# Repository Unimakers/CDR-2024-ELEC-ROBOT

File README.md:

# CDR-2024-ELEC-ROBOT

L'elec du robot de l'équipe Unimakers

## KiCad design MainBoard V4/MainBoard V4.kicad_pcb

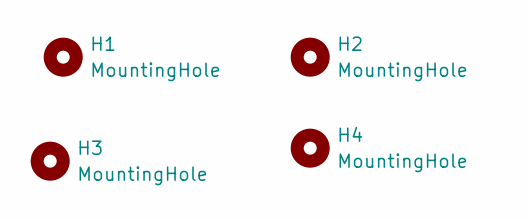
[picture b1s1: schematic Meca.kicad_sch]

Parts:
H1, H2, H3, H4: MountingHole; MountingHole_3.2mm_M3

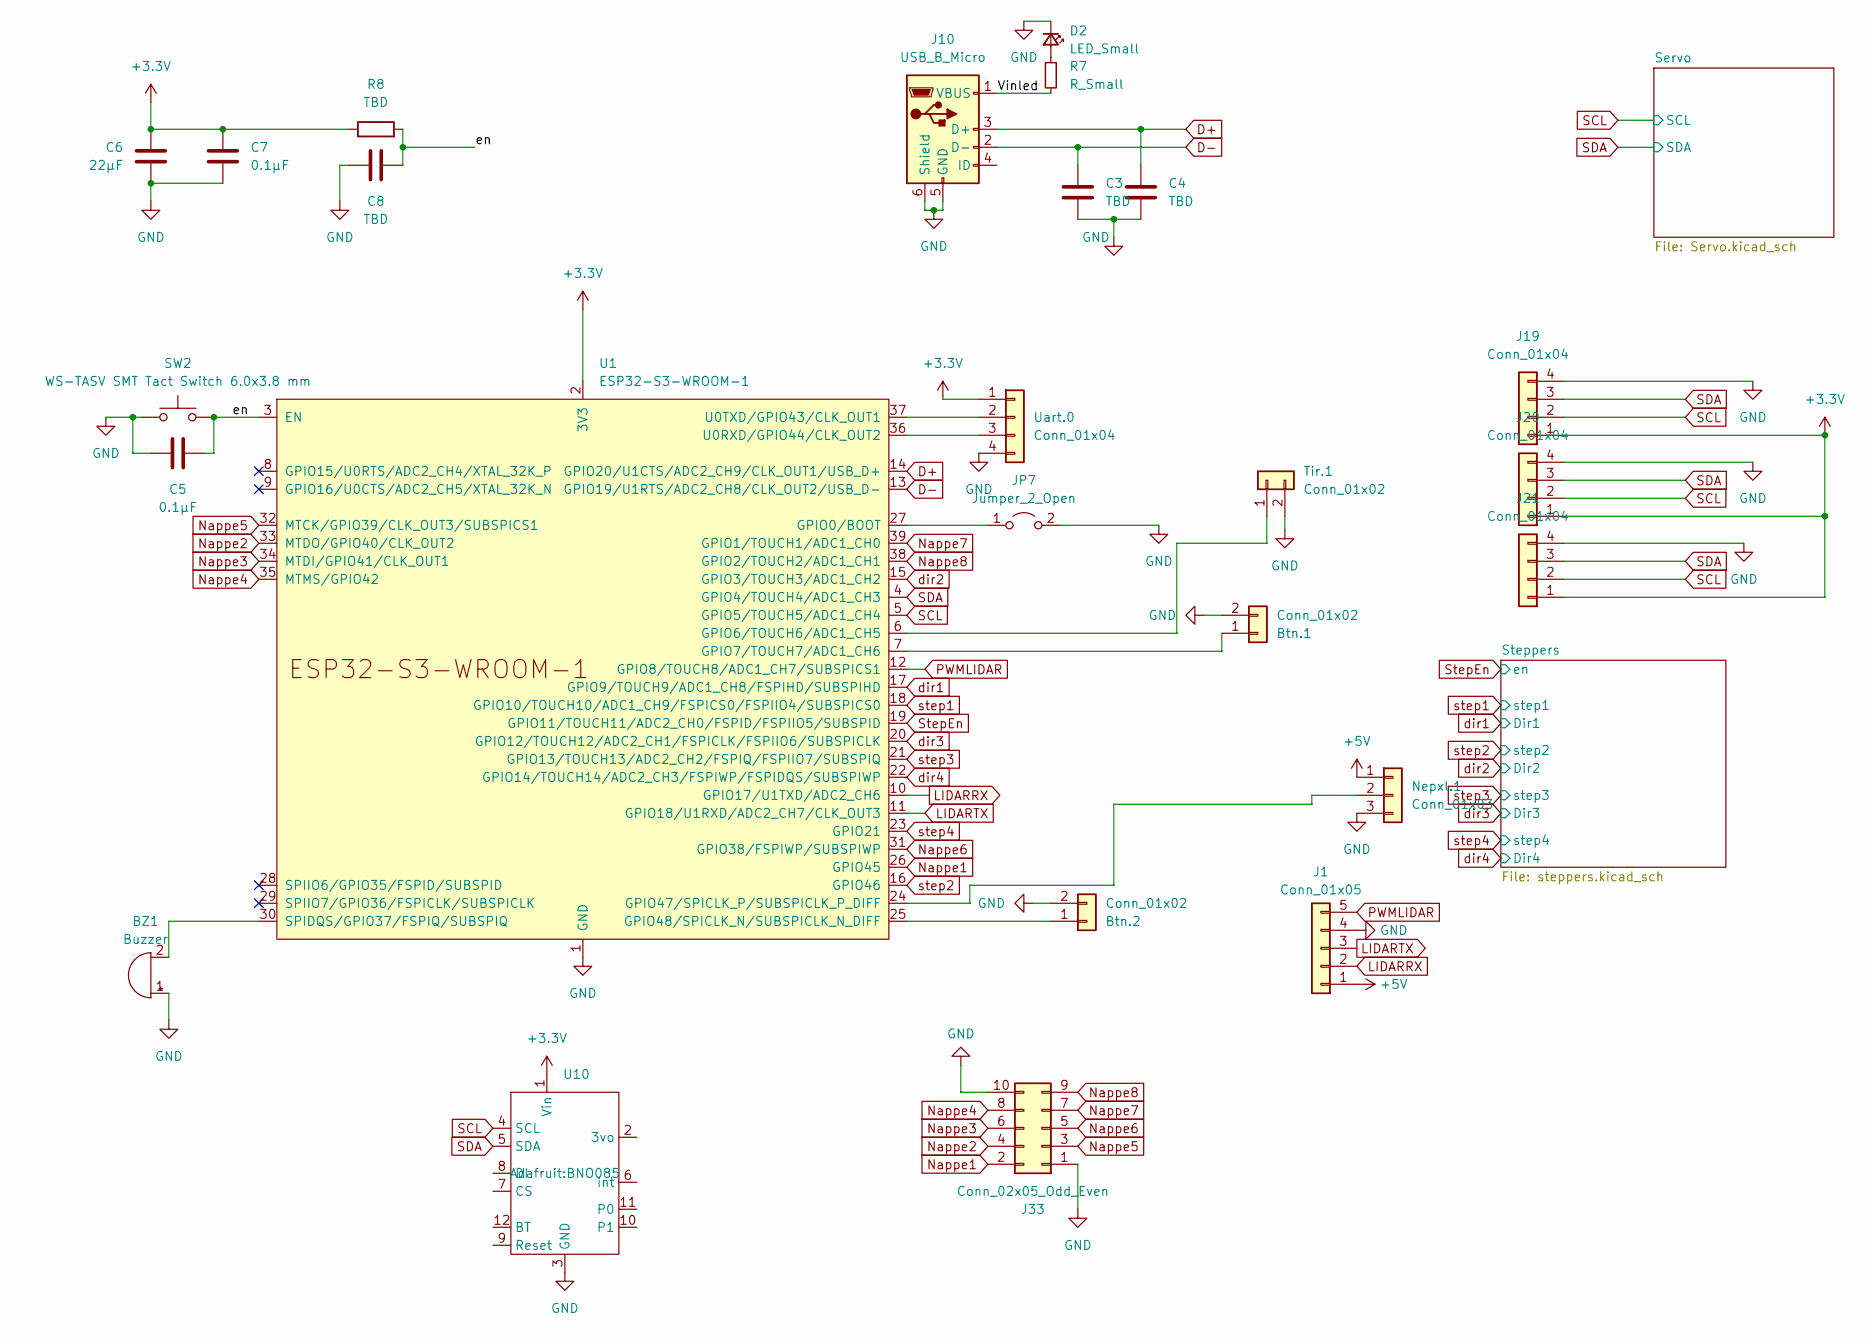
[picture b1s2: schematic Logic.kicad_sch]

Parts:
BZ1: Buzzer; Buzzer_12x9.5RM7.6
Btn.1, Btn.2: Conn_01x02; JST_XH_B2B-XH-A_1x02_P2.50mm_Vertical
C3, C4, C8: TBD; C_0805_2012Metric_Pad1.18x1.45mm_HandSolder
C5, C7: 0.1µF; C_0805_2012Metric_Pad1.18x1.45mm_HandSolder
C6: 22µF; C_0805_2012Metric_Pad1.18x1.45mm_HandSolder
D2: LED_Small; LED_1206_3216Metric_Pad1.42x1.75mm_HandSolder
J1: Conn_01x05; JST_XH_B5B-XH-A_1x05_P2.50mm_Vertical
J10: USB_B_Micro; USB_Micro-B_Wuerth_629105150521
J19, J20, J21: Conn_01x04; JST_XH_B4B-XH-A_1x04_P2.50mm_Vertical
J33: Conn_02x05_Odd_Even; IDC-Header_2x05_P2.54mm_Vertical
JP7: Jumper_2_Open; PinHeader_1x02_P2.54mm_Vertical
Nepxl.1: Conn_01x03; PinSocket_1x03_P2.54mm_Vertical
R7: R_Small; R_1206_3216Metric_Pad1.30x1.75mm_HandSolder
R8: TBD; R_1206_3216Metric_Pad1.30x1.75mm_HandSolder
SW2: WS-TASV SMT Tact Switch 6.0x3.8 mm; WS-TASV SMT Tact Switch
Tir.1: Conn_01x02; JST_XH_B2B-XH-A_1x02_P2.50mm_Vertical
U1: ESP32-S3-WROOM-1
U10: BNO085
Uart.0: Conn_01x04; JST_XH_B4B-XH-A_1x04_P2.50mm_Vertical

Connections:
+3.3V: C6.2, C7.2, J19.1, J20.1, J21.1, R8.1, U1.2 (3V3), U10.1 (Vin), Uart.0.1; also elsewhere on the board
+5V: J1.1, Nepxl.1.1; also elsewhere on the board
/Logic/Vinled: J10.1 (VBUS), R7.2
/Logic/en: C5.2, C8.1, R8.2, SW2.2, U1.3 (EN)
D+: C4.1, J10.3 (D+), U1.14 (GPIO20/U1CTS/ADC2_CH9/CLK_OUT1/USB_D+)
D-: C3.1, J10.2 (D-), U1.13 (GPIO19/U1RTS/ADC2_CH8/CLK_OUT2/USB_D-)
GND: BZ1.1 (-), Btn.1.2, Btn.2.2, C3.2, C4.2, C5.1, C6.1, C7.1, C8.2, D2.1 (K), J1.4, J10.5 (GND), J10.6 (Shield), J19.4, J20.4, J21.4, J33.1, J33.10, JP7.2 (B), Nepxl.1.3, SW2.1, Tir.1.2, U1.1 (GND), U1.40 (GND), U1.41 (GND), U10.3 (GND), Uart.0.4; also elsewhere on the board
LIDARRX: J1.2, U1.10 (GPIO17/U1TXD/ADC2_CH6)
LIDARTX: J1.3, U1.11 (GPIO18/U1RXD/ADC2_CH7/CLK_OUT3)
Nappe1: J33.2, U1.26 (GPIO45)
Nappe2: J33.4, U1.33 (MTDO/GPIO40/CLK_OUT2)
Nappe3: J33.6, U1.34 (MTDI/GPIO41/CLK_OUT1)
Nappe4: J33.8, U1.35 (MTMS/GPIO42)
Nappe5: J33.3, U1.32 (MTCK/GPIO39/CLK_OUT3/SUBSPICS1)
Nappe6: J33.5, U1.31 (GPIO38/FSPIWP/SUBSPIWP)
Nappe7: J33.7, U1.39 (GPIO1/TOUCH1/ADC1_CH0)
Nappe8: J33.9, U1.38 (GPIO2/TOUCH2/ADC1_CH1)
unnamed: BZ1.2 (+), U1.30 (SPIDQS/GPIO37/FSPIQ/SUBSPIQ)
unnamed: Btn.1.1, U1.7 (GPIO7/TOUCH7/ADC1_CH6)
unnamed: Btn.2.1, U1.25 (GPIO48/SPICLK_N/SUBSPICLK_N_DIFF)
unnamed: D2.2 (A), R7.1
unnamed: JP7.1 (A), U1.27 (GPIO0/BOOT)
unnamed: Nepxl.1.2, U1.24 (GPIO47/SPICLK_P/SUBSPICLK_P_DIFF)
unnamed: Tir.1.1, U1.6 (GPIO6/TOUCH6/ADC1_CH5)
unnamed: U1.36 (U0RXD/GPIO44/CLK_OUT2), Uart.0.3
unnamed: U1.37 (U0TXD/GPIO43/CLK_OUT1), Uart.0.2
PWMLIDAR: J1.5, U1.12 (GPIO8/TOUCH8/ADC1_CH7/SUBSPICS1)
SCL: J19.2, J20.2, J21.2, U1.5 (GPIO5/TOUCH5/ADC1_CH4), U10.4 (SCL); also elsewhere on the board
SDA: J19.3, J20.3, J21.3, U1.4 (GPIO4/TOUCH4/ADC1_CH3), U10.5 (SDA); also elsewhere on the board
StepEn: U1.19 (GPIO11/TOUCH11/ADC2_CH0/FSPID/FSPIIO5/S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); also elsewhere on the board
dir1: U1.17 (GPIO9/TOUCH9/ADC1_CH8/FSPIHD/SUBSPIHD); also elsewhere on the board
dir2: U1.15 (GPIO3/TOUCH3/ADC1_CH2); also elsewhere on the board
dir3: U1.20 (GPIO12/TOUCH12/ADC2_CH1/FSPICLK/FSPIIO6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); also elsewhere on the board
dir4: U1.22 (GPIO14/TOUCH14/ADC2_CH3/FSPIWP/FSPIDQS/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); also elsewhere on the board
step1: U1.18 (GPIO10/TOUCH10/ADC1_CH9/FSPICS0/FSPIIO4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); also elsewhere on the board
step2: U1.16 (GPIO46); also elsewhere on the board
step3: U1.21 (GPIO13/TOUCH13/ADC2_CH2/FSPIQ/FSPIIO7/S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); also elsewhere on the board
step4: U1.23 (GPIO21); also elsewhere on the board

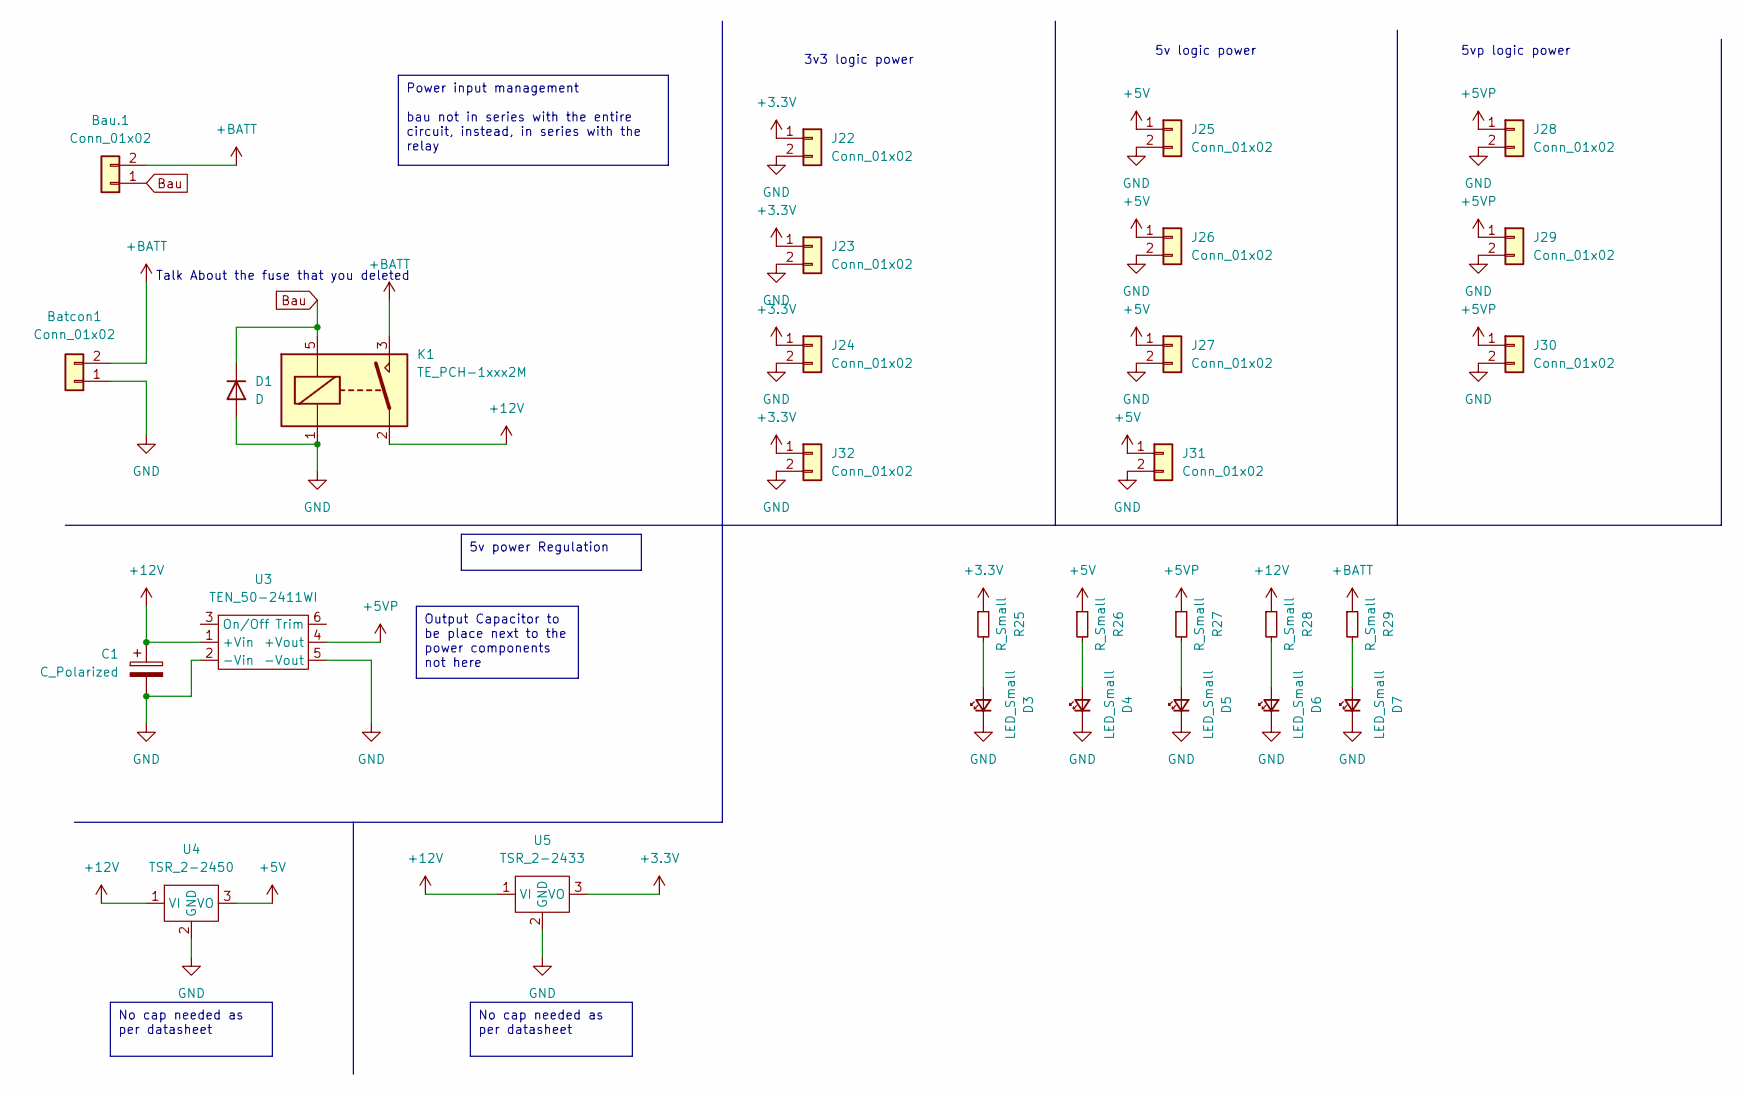
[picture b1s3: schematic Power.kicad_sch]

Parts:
Batcon1: Conn_01x02; AMASS_XT60-F_1x02_P7.20mm_Vertical
Bau.1: Conn_01x02; Molex_KK-254_AE-6410-02A_1x02_P2.54mm_Vertical
C1: C_Polarized
D1: D; D_DO-35_SOD27_P10.16mm_Horizontal
D3, D4, D5, D6, D7: LED_Small; LED_1206_3216Metric_Pad1.42x1.75mm_HandSolder
J22, J23, J24, J25, J26, J27, J28, J29, J30, J31, J32: Conn_01x02; Molex_KK-254_AE-6410-02A_1x02_P2.54mm_Vertical
K1: TE_PCH-1xxx2M; Relay_SPST_TE_PCH-1xxx2M
R25, R26, R27, R28, R29: R_Small; LED_1206_3216Metric_Pad1.42x1.75mm_HandSolder
U3: TEN_50-2411WI; Traco TEN 50 series
U4: TSR_2-2450; Traco 2- 24xx
U5: TSR_2-2433; Traco 2- 24xx

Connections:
+3.3V: J22.1, J23.1, J24.1, J32.1, R25.1, U5.3 (VO); also elsewhere on the board
+5V: J25.1, J26.1, J27.1, J31.1, R26.1, U4.3 (VO); also elsewhere on the board
+5VP: J28.1, J29.1, J30.1, R27.1, U3.4 (+Vout); also elsewhere on the board
+12V: C1.1, K1.2, R28.1, U3.1 (+Vin), U4.1 (VI), U5.1 (VI); also elsewhere on the board
+BATT: Batcon1.2, Bau.1.2, K1.3, R29.1
Bau: Bau.1.1, D1.1 (K), K1.5
GND: Batcon1.1, C1.2, D1.2 (A), D3.1 (K), D4.1 (K), D5.1 (K), D6.1 (K), D7.1 (K), J22.2, J23.2, J24.2, J25.2, J26.2, J27.2, J28.2, J29.2, J30.2, J31.2, J32.2, K1.1, U3.2 (-Vin), U3.5 (-Vout), U4.2 (GND), U5.2 (GND); also elsewhere on the board
unnamed: D3.2 (A), R25.2
unnamed: D4.2 (A), R26.2
unnamed: D5.2 (A), R27.2
unnamed: D6.2 (A), R28.2
unnamed: D7.2 (A), R29.2

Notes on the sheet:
Output Capacitor to be place next to the power components not here
5v power Regulation
No cap needed as per datasheet
Power input management bau not in series with the entire circuit, instead, in series with the relay
5vp logic power
Talk About the fuse that you deleted
5v logic power
3v3 logic power

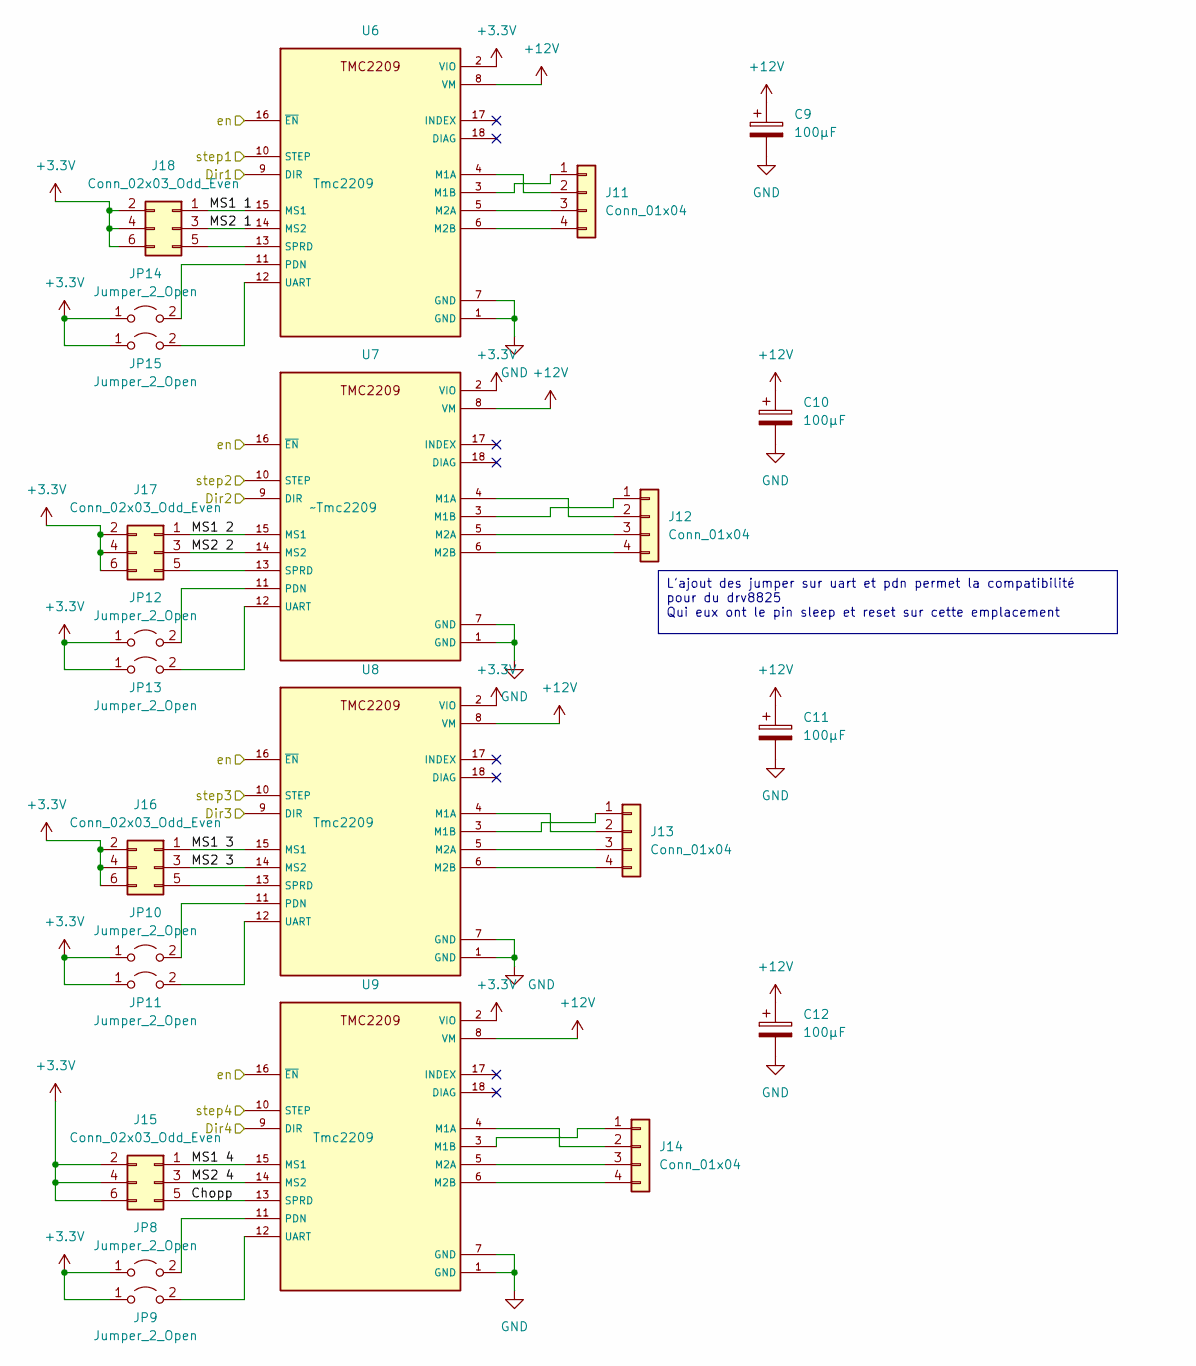
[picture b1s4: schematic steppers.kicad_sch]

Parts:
C9, C10, C11, C12: 100µF; CP_Elec_10x10.5
J11, J12, J13, J14: Conn_01x04; Molex_KK-254_AE-6410-04A_1x04_P2.54mm_Vertical
J15, J16, J17, J18: Conn_02x03_Odd_Even; PinHeader_2x03_P2.54mm_Vertical
JP8, JP9, JP10, JP11, JP12, JP13, JP14, JP15: Jumper_2_Open; SolderJumper-2_P1.3mm_Open_Pad1.0x1.5mm
U6, U8, U9: Tmc2209; BOB_TMC2209_SILENTSTEPSTICK
U7: ~Tmc2209; BOB_TMC2209_SILENTSTEPSTICK

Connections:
+3.3V: J15.2, J15.4, J15.6, J16.2, J16.4, J16.6, J17.2, J17.4, J17.6, J18.2, J18.4, J18.6, JP8.1 (A), JP9.1 (A), JP10.1 (A), JP11.1 (A), JP12.1 (A), JP13.1 (A), JP14.1 (A), JP15.1 (A), U6.2 (VIO), U7.2 (VIO), U8.2 (VIO), U9.2 (VIO); also elsewhere on the board
+12V: C9.1, C10.1, C11.1, C12.1, U6.8 (VM), U7.8 (VM), U8.8 (VM), U9.8 (VM); also elsewhere on the board
/Logic/Steppers/Chopp: J15.5, U9.13 (SPRD)
/Logic/Steppers/MS1 1: J18.1, U6.15 (MS1)
/Logic/Steppers/MS1 2: J17.1, U7.15 (MS1)
/Logic/Steppers/MS1 3: J16.1, U8.15 (MS1)
/Logic/Steppers/MS1 4: J15.1, U9.15 (MS1)
/Logic/Steppers/MS2 1: J18.3, U6.14 (MS2)
/Logic/Steppers/MS2 2: J17.3, U7.14 (MS2)
/Logic/Steppers/MS2 3: J16.3, U8.14 (MS2)
/Logic/Steppers/MS2 4: J15.3, U9.14 (MS2)
GND: C9.2, C10.2, C11.2, C12.2, U6.1 (GND), U6.7 (GND), U7.1 (GND), U7.7 (GND), U8.1 (GND), U8.7 (GND), U9.1 (GND), U9.7 (GND); also elsewhere on the board
unnamed: J11.1, U6.3 (M1B)
unnamed: J11.2, U6.4 (M1A)
unnamed: J11.3, U6.5 (M2A)
unnamed: J11.4, U6.6 (M2B)
unnamed: J12.1, U7.3 (M1B)
unnamed: J12.2, U7.4 (M1A)
unnamed: J12.3, U7.5 (M2A)
unnamed: J12.4, U7.6 (M2B)
unnamed: J13.1, U8.3 (M1B)
unnamed: J13.2, U8.4 (M1A)
unnamed: J13.3, U8.5 (M2A)
unnamed: J13.4, U8.6 (M2B)
unnamed: J14.1, U9.3 (M1B)
unnamed: J14.2, U9.4 (M1A)
unnamed: J14.3, U9.5 (M2A)
unnamed: J14.4, U9.6 (M2B)
unnamed: J16.5, U8.13 (SPRD)
unnamed: J17.5, U7.13 (SPRD)
unnamed: J18.5, U6.13 (SPRD)
unnamed: JP8.2 (B), U9.11 (PDN)
unnamed: JP9.2 (B), U9.12 (UART)
unnamed: JP10.2 (B), U8.11 (PDN)
unnamed: JP11.2 (B), U8.12 (UART)
unnamed: JP12.2 (B), U7.11 (PDN)
unnamed: JP13.2 (B), U7.12 (UART)
unnamed: JP14.2 (B), U6.11 (PDN)
unnamed: JP15.2 (B), U6.12 (UART)
StepEn: U6.16 (~EN), U7.16 (~EN), U8.16 (~EN), U9.16 (~EN); also elsewhere on the board
dir1: U6.9 (DIR); also elsewhere on the board
dir2: U7.9 (DIR); also elsewhere on the board
dir3: U8.9 (DIR); also elsewhere on the board
dir4: U9.9 (DIR); also elsewhere on the board
step1: U6.10 (STEP); also elsewhere on the board
step2: U7.10 (STEP); also elsewhere on the board
step3: U8.10 (STEP); also elsewhere on the board
step4: U9.10 (STEP); also elsewhere on the board

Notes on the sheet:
L'ajout des jumper sur uart et pdn permet la compatibilité pour du drv8825 Qui eux ont le pin sleep et reset sur cette emplacement

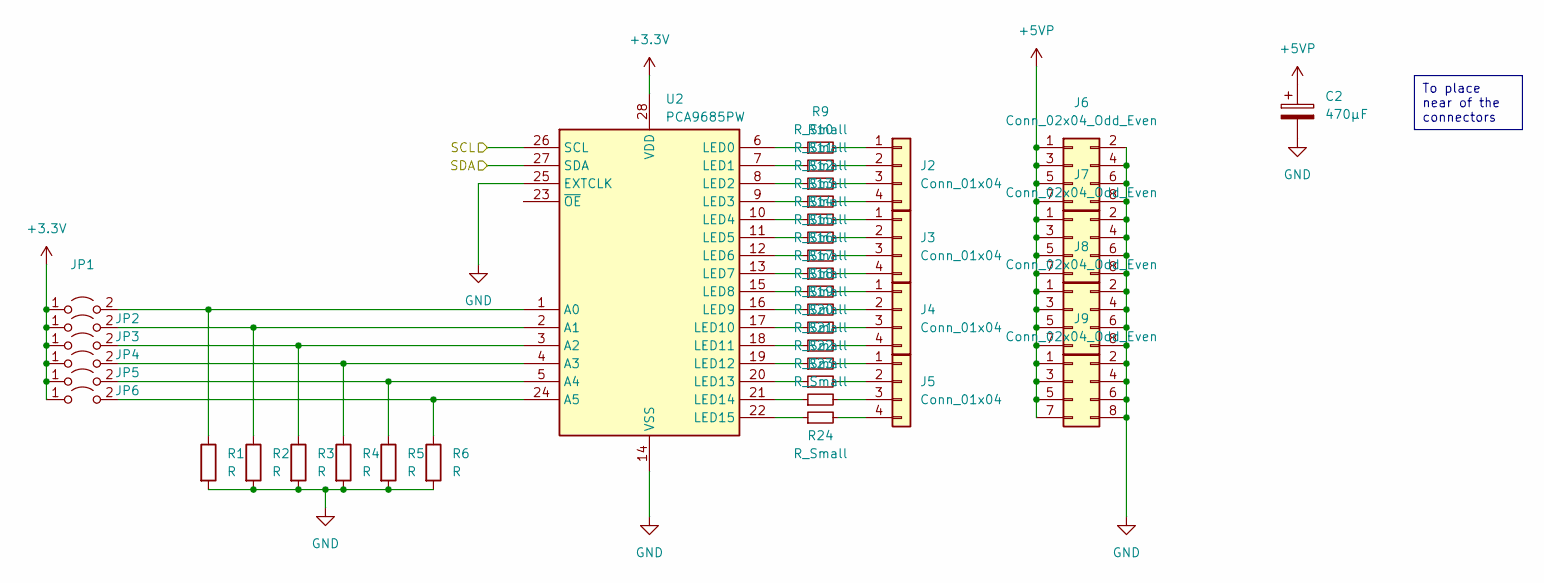
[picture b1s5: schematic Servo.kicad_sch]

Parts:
C2: 470µF; CP_Elec_10x10.5
J2, J3, J4, J5: Conn_01x04; PinHeader_1x04_P2.54mm_Vertical
J6, J7, J8, J9: Conn_02x04_Odd_Even; PinHeader_2x04_P2.54mm_Vertical
JP1, JP2, JP3, JP4, JP5, JP6: Jumper_2_Open; SolderJumper-2_P1.3mm_Open_Pad1.0x1.5mm
R1, R2, R3, R4, R5, R6: R; R_1206_3216Metric_Pad1.30x1.75mm_HandSolder
R9, R10, R11, R12, R13, R14, R15, R16, R17, R18, R19, R20, R21, R22, R23, R24: R_Small; R_1206_3216Metric_Pad1.30x1.75mm_HandSolder
U2: PCA9685PW; TSSOP-28_4.4x9.7mm_P0.65mm

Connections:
+3.3V: JP1.1 (A), JP2.1 (A), JP3.1 (A), JP4.1 (A), JP5.1 (A), JP6.1 (A), U2.28 (VDD); also elsewhere on the board
+5VP: C2.1, J6.1, J6.3, J6.5, J6.7, J7.1, J7.3, J7.5, J7.7, J8.1, J8.3, J8.5, J8.7, J9.1, J9.3, J9.5, J9.7; also elsewhere on the board
GND: C2.2, J6.2, J6.4, J6.6, J6.8, J7.2, J7.4, J7.6, J7.8, J8.2, J8.4, J8.6, J8.8, J9.2, J9.4, J9.6, J9.8, R1.2, R2.2, R3.2, R4.2, R5.2, R6.2, U2.14 (VSS), U2.25 (EXTCLK); also elsewhere on the board
unnamed: J2.1, R9.2
unnamed: J2.2, R10.2
unnamed: J2.3, R11.2
unnamed: J2.4, R12.2
unnamed: J3.1, R13.2
unnamed: J3.2, R14.2
unnamed: J3.3, R15.2
unnamed: J3.4, R16.2
unnamed: J4.1, R17.2
unnamed: J4.2, R18.2
unnamed: J4.3, R19.2
unnamed: J4.4, R20.2
unnamed: J5.1, R21.2
unnamed: J5.2, R22.2
unnamed: J5.3, R23.2
unnamed: J5.4, R24.2
unnamed: JP1.2 (B), R1.1, U2.1 (A0)
unnamed: JP2.2 (B), R2.1, U2.2 (A1)
unnamed: JP3.2 (B), R3.1, U2.3 (A2)
unnamed: JP4.2 (B), R4.1, U2.4 (A3)
unnamed: JP5.2 (B), R5.1, U2.5 (A4)
unnamed: JP6.2 (B), R6.1, U2.24 (A5)
unnamed: R9.1, U2.6 (LED0)
unnamed: R10.1, U2.7 (LED1)
unnamed: R11.1, U2.8 (LED2)
unnamed: R12.1, U2.9 (LED3)
unnamed: R13.1, U2.10 (LED4)
unnamed: R14.1, U2.11 (LED5)
unnamed: R15.1, U2.12 (LED6)
unnamed: R16.1, U2.13 (LED7)
unnamed: R17.1, U2.15 (LED8)
unnamed: R18.1, U2.16 (LED9)
unnamed: R19.1, U2.17 (LED10)
unnamed: R20.1, U2.18 (LED11)
unnamed: R21.1, U2.19 (LED12)
unnamed: R22.1, U2.20 (LED13)
unnamed: R23.1, U2.21 (LED14)
unnamed: R24.1, U2.22 (LED15)
SCL: U2.26 (SCL); also elsewhere on the board
SDA: U2.27 (SDA); also elsewhere on the board

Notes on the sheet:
To place near of the connectors

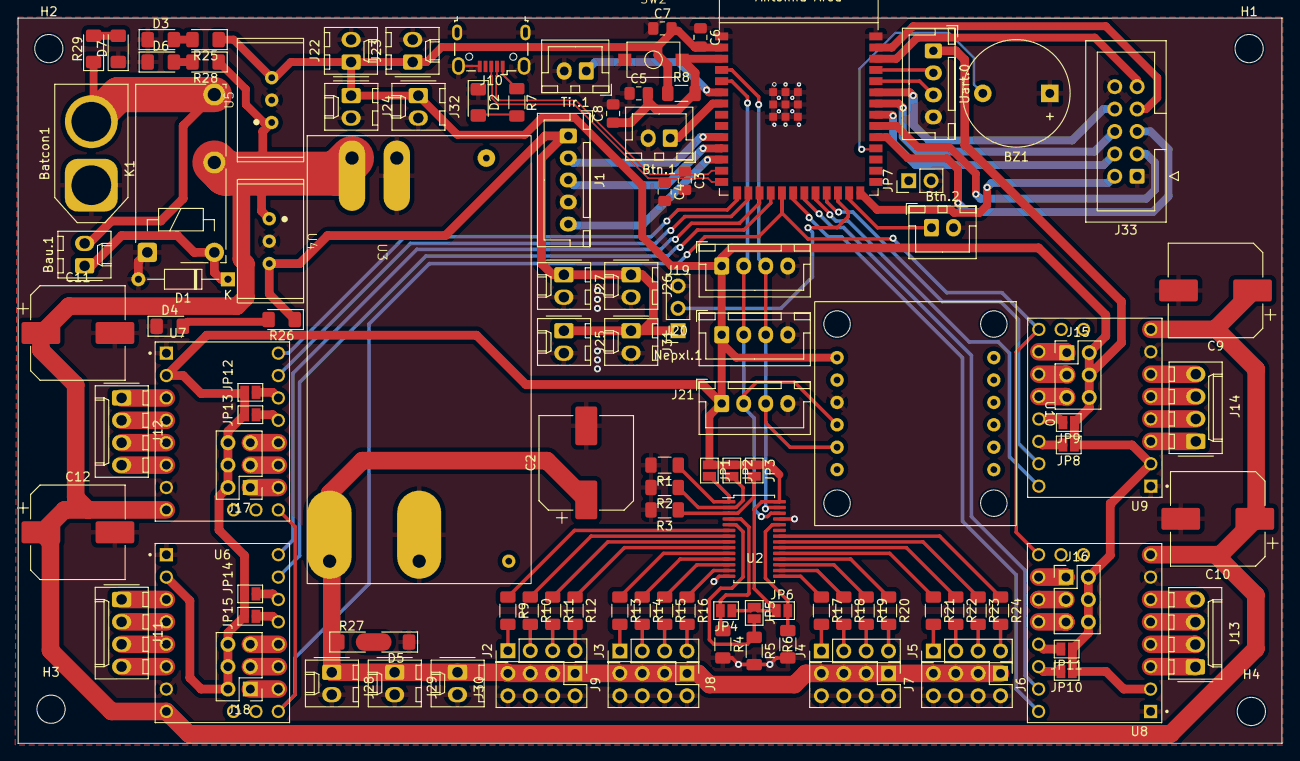
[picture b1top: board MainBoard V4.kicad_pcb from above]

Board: 2 copper layers, 143.3 x 82.3 mm, 119 parts (0 on the bottom side), 121 nets.

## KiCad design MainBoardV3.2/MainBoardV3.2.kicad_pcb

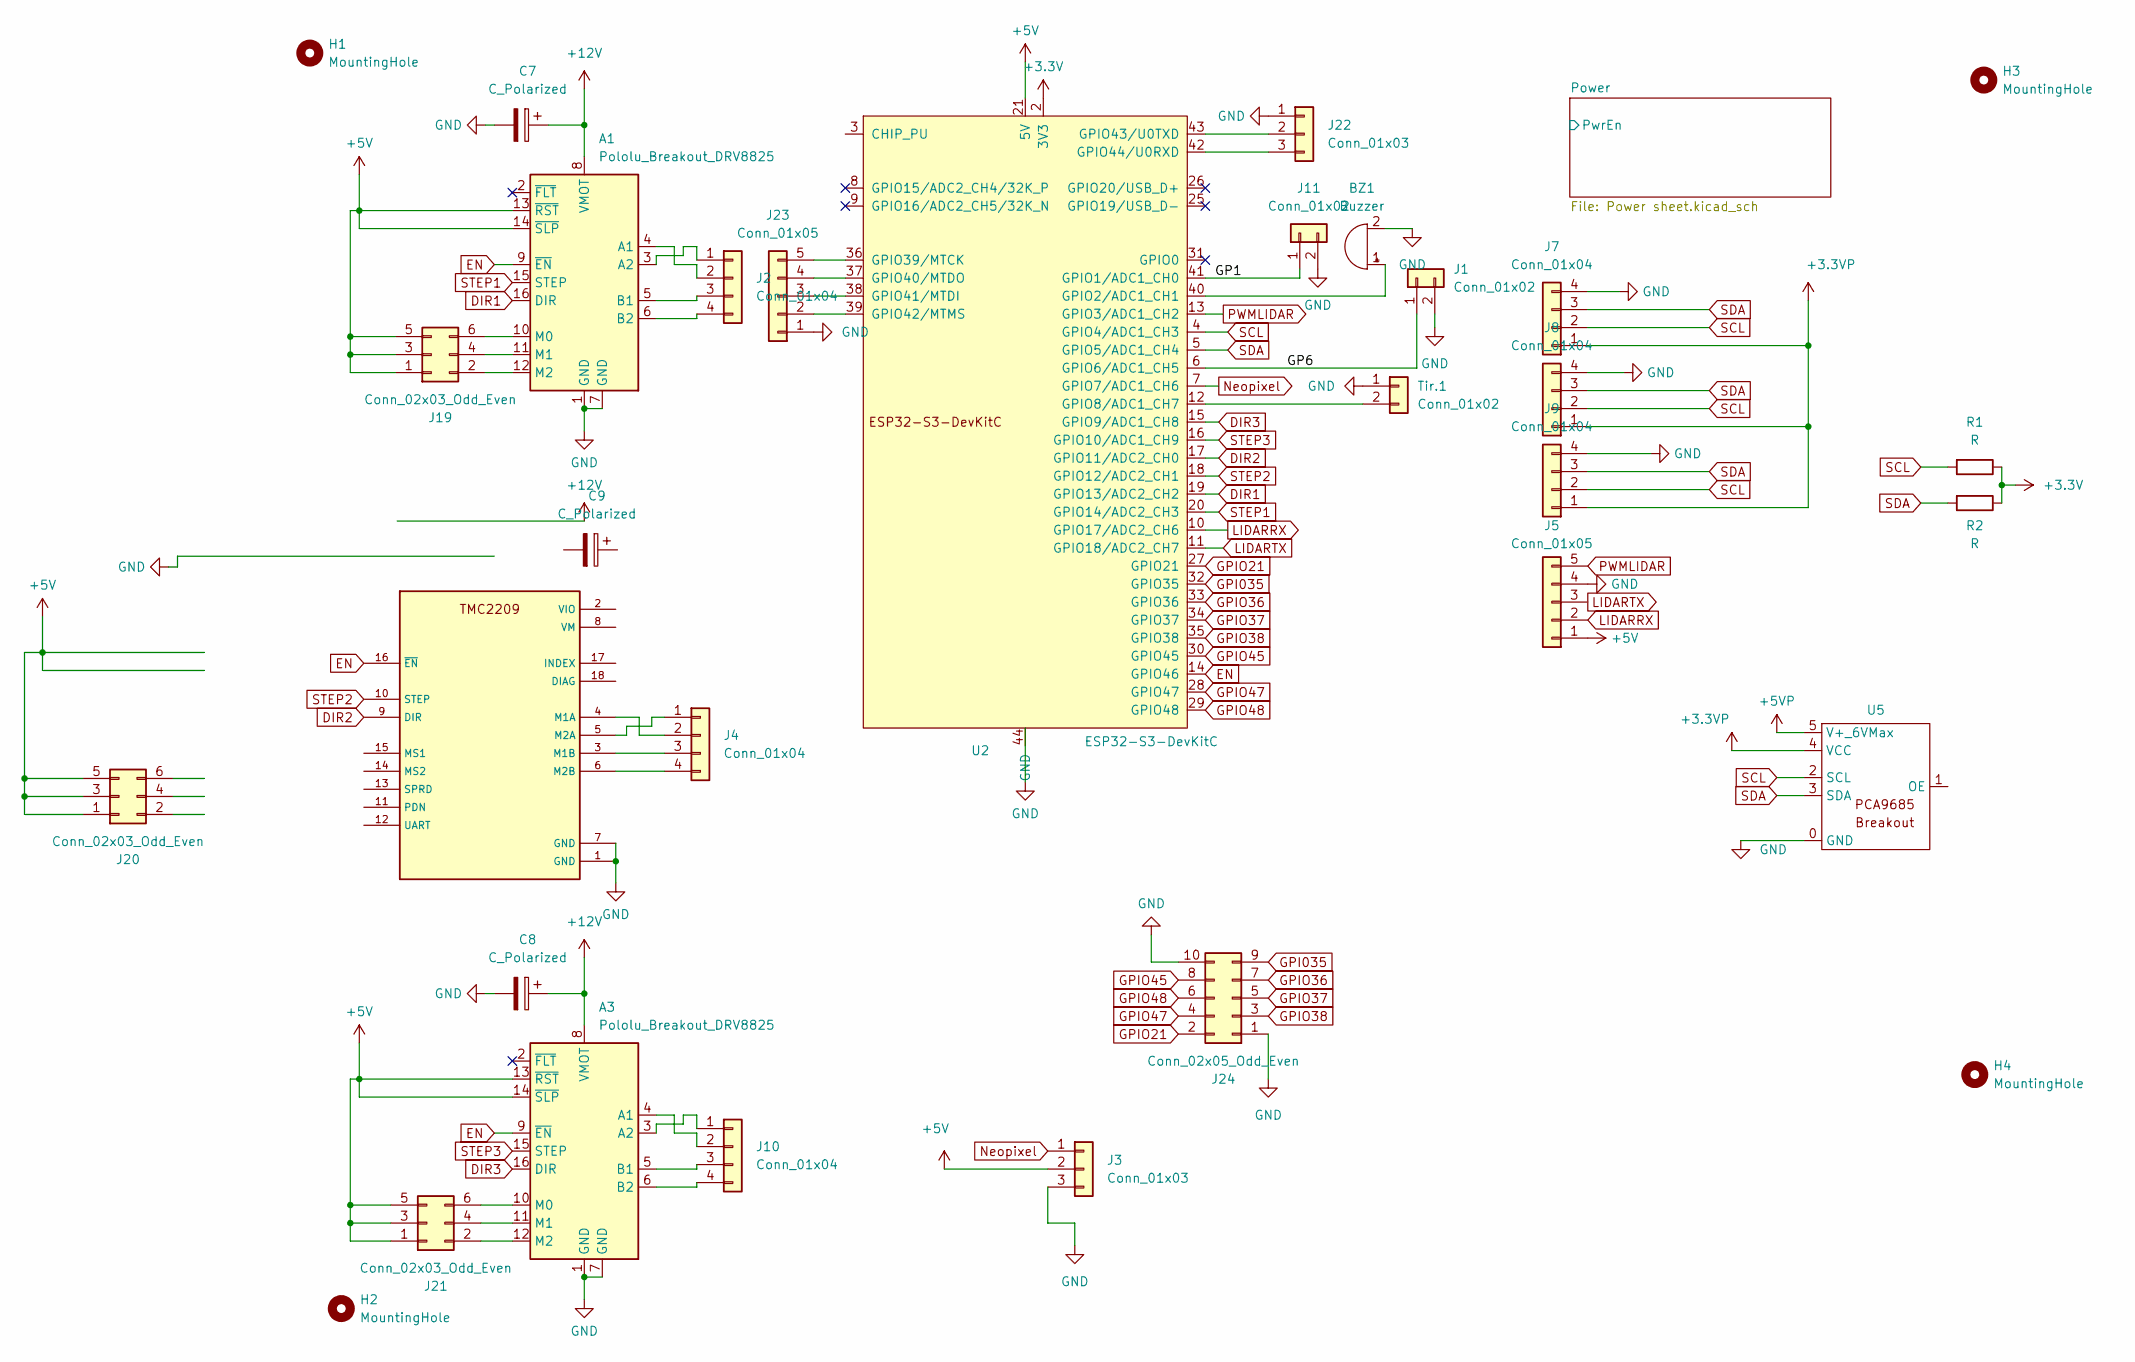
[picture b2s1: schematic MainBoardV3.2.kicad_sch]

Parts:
A1, A3: Pololu_Breakout_DRV8825; Pololu_Breakout-16_15.2x20.3mm
BZ1: Buzzer; Buzzer_12x9.5RM7.6
C7, C8, C9: C_Polarized; CP_Elec_6.3x4.9
H1, H2, H3, H4: MountingHole; MountingHole_3.2mm_M3
J1, J11: Conn_01x02; JST_XH_B2B-XH-A_1x02_P2.50mm_Vertical
J2, J4, J10: Conn_01x04; Molex_KK-254_AE-6410-04A_1x04_P2.54mm_Vertical
J3, J22: Conn_01x03; PinHeader_1x03_P2.54mm_Vertical
J5, J23: Conn_01x05; JST_XH_B5B-XH-A_1x05_P2.50mm_Vertical
J7, J8, J9: Conn_01x04; JST_XH_B4B-XH-A_1x04_P2.50mm_Vertical
J19, J20, J21: Conn_02x03_Odd_Even; PinHeader_2x03_P2.54mm_Vertical
J24: Conn_02x05_Odd_Even; IDC-Header_2x05_P2.54mm_Vertical
R1, R2: R; R_1206_3216Metric_Pad1.30x1.75mm_HandSolder
Tir.1: Conn_01x02; JST_XH_B2B-XH-A_1x02_P2.50mm_Vertical
U2: ESP32-S3-DevKitC
U5: PCA9685breakout
U6: (no value)

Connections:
+3.3V: R1.1, R2.1, U2.1 (3V3), U2.2 (3V3)
+5VP: U5.5 (V+_6VMax); also elsewhere on the board
/GP1: J11.1, U2.41 (GPIO1/ADC1_CH0)
/GP6: J1.1, U2.6 (GPIO6/ADC1_CH5)
DIR1: A1.16 (DIR), U2.19 (GPIO13/ADC2_CH2)
DIR2: U2.17 (GPIO11/ADC2_CH0), U6.9 (DIR); also elsewhere on the board
DIR3: A3.16 (DIR), U2.15 (GPIO9/ADC1_CH8)
EN: A1.9 (~EN), A3.9 (~EN), U2.14 (GPIO46), U6.16 (~EN); also elsewhere on the board
GND: A1.1 (GND), A1.7 (GND), A3.1 (GND), A3.7 (GND), BZ1.2 (+), C7.2, C8.2, C9.2, J1.2, J3.3, J5.4, J7.4, J8.4, J9.4, J11.2, J22.1, J23.1, J24.1, J24.10, Tir.1.1, U2.22 (GND), U2.23 (GND), U2.24 (GND), U2.44 (GND), U5.0 (GND), U6.1 (GND), U6.7 (GND); also elsewhere on the board
GPI035: J24.9, U2.32 (GPIO35)
GPIO21: J24.2, U2.27 (GPIO21)
GPIO36: J24.7, U2.33 (GPIO36)
GPIO37: J24.5, U2.34 (GPIO37)
GPIO38: J24.3, U2.35 (GPIO38)
GPIO45: J24.8, U2.30 (GPIO45)
GPIO47: J24.4, U2.28 (GPIO47)
GPIO48: J24.6, U2.29 (GPIO48)
LIDARRX: J5.2, U2.10 (GPIO17/ADC2_CH6)
LIDARTX: J5.3, U2.11 (GPIO18/ADC2_CH7)
Neopixel: J3.1, U2.7 (GPIO7/ADC1_CH6)
unnamed: A1.4 (A1), J2.2
unnamed: A1.3 (A2), J2.1
unnamed: A1.5 (B1), J2.3
unnamed: A1.6 (B2), J2.4
unnamed: A1.10 (M0), J19.6
unnamed: A1.11 (M1), J19.4
unnamed: A1.12 (M2), J19.2
unnamed 28: J4.2, U6.4 (M1A); also elsewhere on the board
unnamed 29: J4.1, U6.5 (M2A); also elsewhere on the board
unnamed 30: J4.3, U6.3 (M1B); also elsewhere on the board
unnamed 31: J4.4, U6.6 (M2B); also elsewhere on the board
unnamed 32: J20.6; also elsewhere on the board
unnamed 33: J20.4; also elsewhere on the board
unnamed 34: J20.2; also elsewhere on the board
unnamed: A3.4 (A1), J10.2
unnamed: A3.3 (A2), J10.1
unnamed: A3.5 (B1), J10.3
unnamed: A3.6 (B2), J10.4
unnamed: A3.10 (M0), J21.6
unnamed: A3.11 (M1), J21.4
unnamed: A3.12 (M2), J21.2
unnamed: BZ1.1 (-), U2.40 (GPIO2/ADC1_CH1)
unnamed: J22.2, U2.43 (GPIO43/U0TXD)
unnamed: J22.3, U2.42 (GPIO44/U0RXD)
unnamed: J23.2, U2.39 (GPIO42/MTMS)
unnamed: J23.3, U2.38 (GPIO41/MTDI)
unnamed: J23.4, U2.37 (GPIO40/MTDO)
unnamed: J23.5, U2.36 (GPIO39/MTCK)
unnamed: Tir.1.2, U2.12 (GPIO8/ADC1_CH7)
PWMLIDAR: J5.5, U2.13 (GPIO3/ADC1_CH2)
SCL: J7.2, J8.2, J9.2, R1.2, U2.4 (GPIO4/ADC1_CH3), U5.2 (SCL)
SDA: J7.3, J8.3, J9.3, R2.2, U2.5 (GPIO5/ADC1_CH4), U5.3 (SDA)
STEP1: A1.15 (STEP), U2.20 (GPIO14/ADC2_CH3)
STEP2: U2.18 (GPIO12/ADC2_CH1), U6.10 (STEP); also elsewhere on the board
STEP3: A3.15 (STEP), U2.16 (GPIO10/ADC1_CH9)

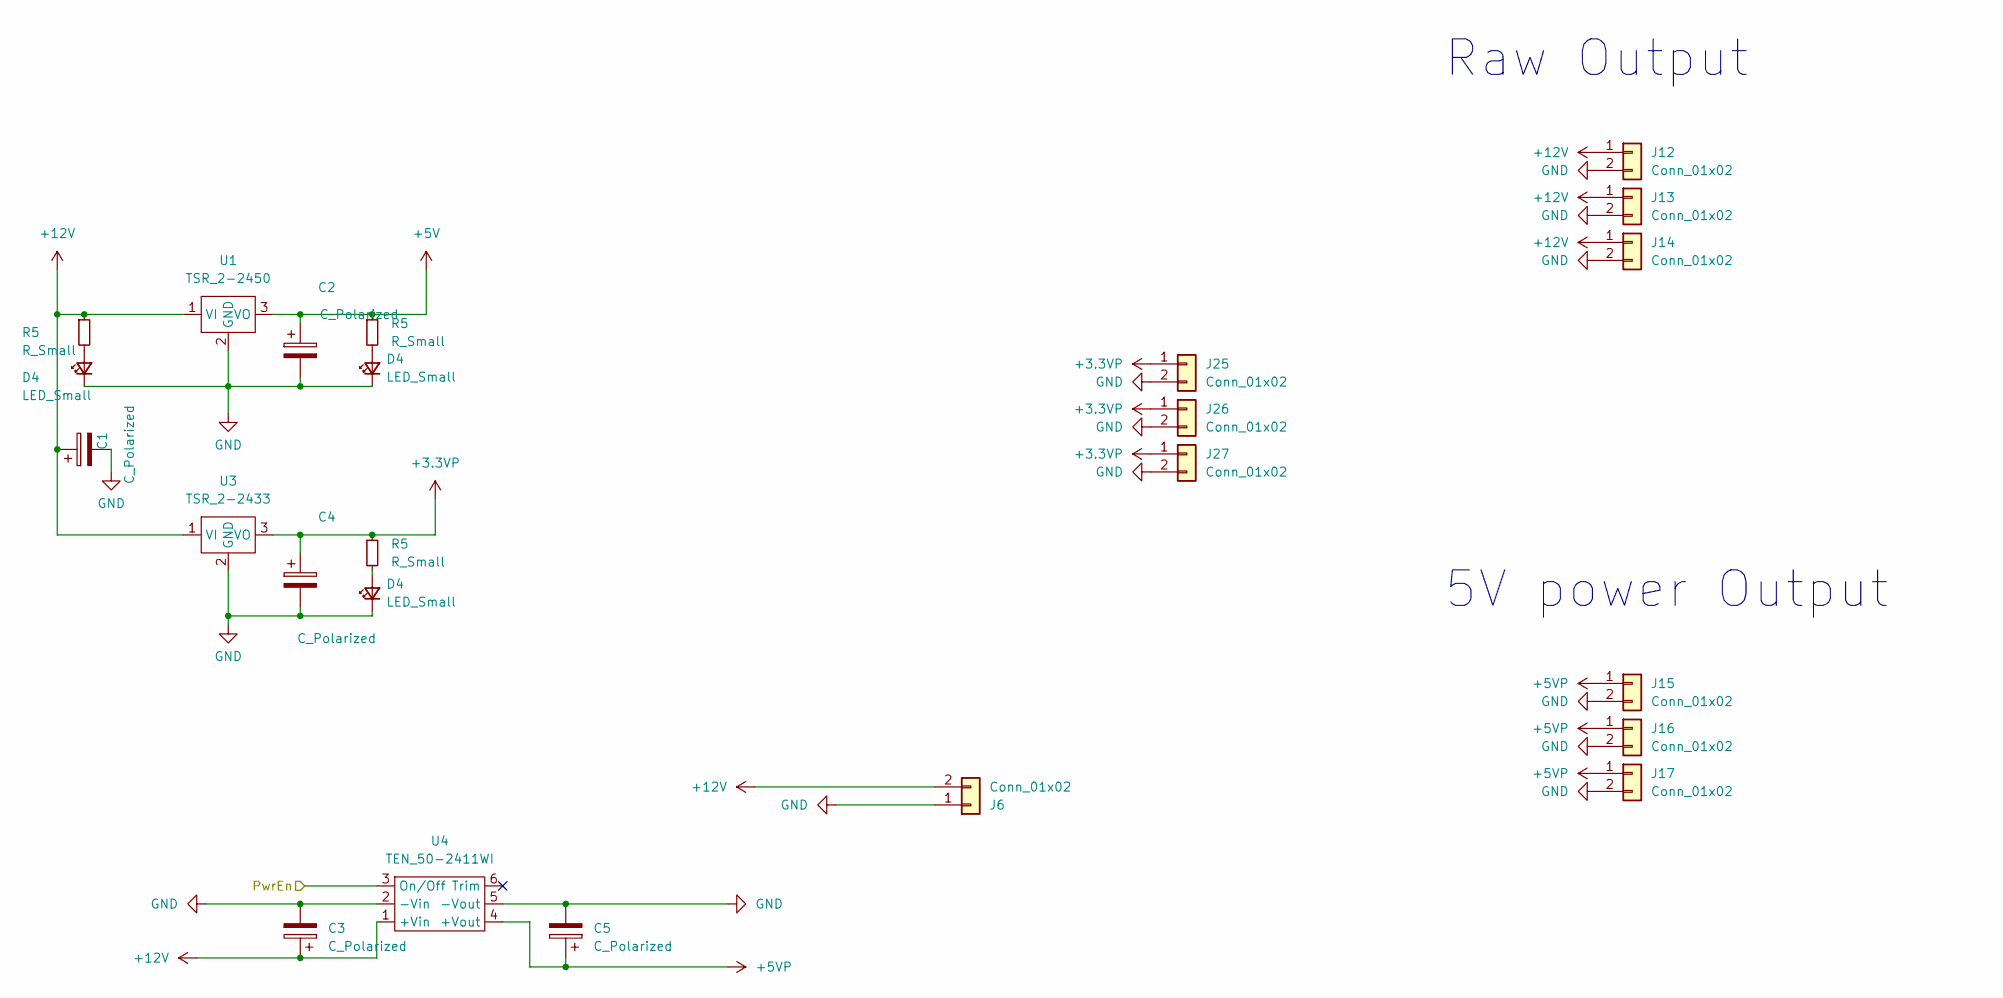
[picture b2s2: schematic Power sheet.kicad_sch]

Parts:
C1, C5: C_Polarized; CP_Elec_6.3x5.9
C2, C4: C_Polarized; CP_Radial_D5.0mm_P2.50mm
C3: C_Polarized; CP_Elec_10x12.6
D4: LED_Small; LED_1206_3216Metric_Pad1.42x1.75mm_HandSolder
J6: Conn_01x02; AMASS_XT60-M_1x02_P7.20mm_Vertical
J12, J13, J14, J15, J16, J17, J25, J26, J27: Conn_01x02; Molex_KK-254_AE-6410-02A_1x02_P2.54mm_Vertical
R5: R_Small; R_1206_3216Metric_Pad1.30x1.75mm_HandSolder
U1: TSR_2-2450; Traco 2- 24xx
U3: TSR_2-2433; Traco 2- 24xx
U4: TEN_50-2411WI; Traco TEN 50 series

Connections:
+5VP: C5.1, J15.1, J16.1, J17.1, U4.4 (+Vout); also elsewhere on the board
/Power/PwrEn: U4.3 (On/Off)
GND: C1.2, C2.2, C3.2, C4.2, C5.2, D4.1 (K), J6.1, J12.2, J13.2, J14.2, J15.2, J16.2, J17.2, J25.2, J26.2, J27.2, U1.2 (GND), U3.2 (GND), U4.2 (-Vin), U4.5 (-Vout); also elsewhere on the board
unnamed: D4.2 (A), R5.2

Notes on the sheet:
5V power Output
Raw Output

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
